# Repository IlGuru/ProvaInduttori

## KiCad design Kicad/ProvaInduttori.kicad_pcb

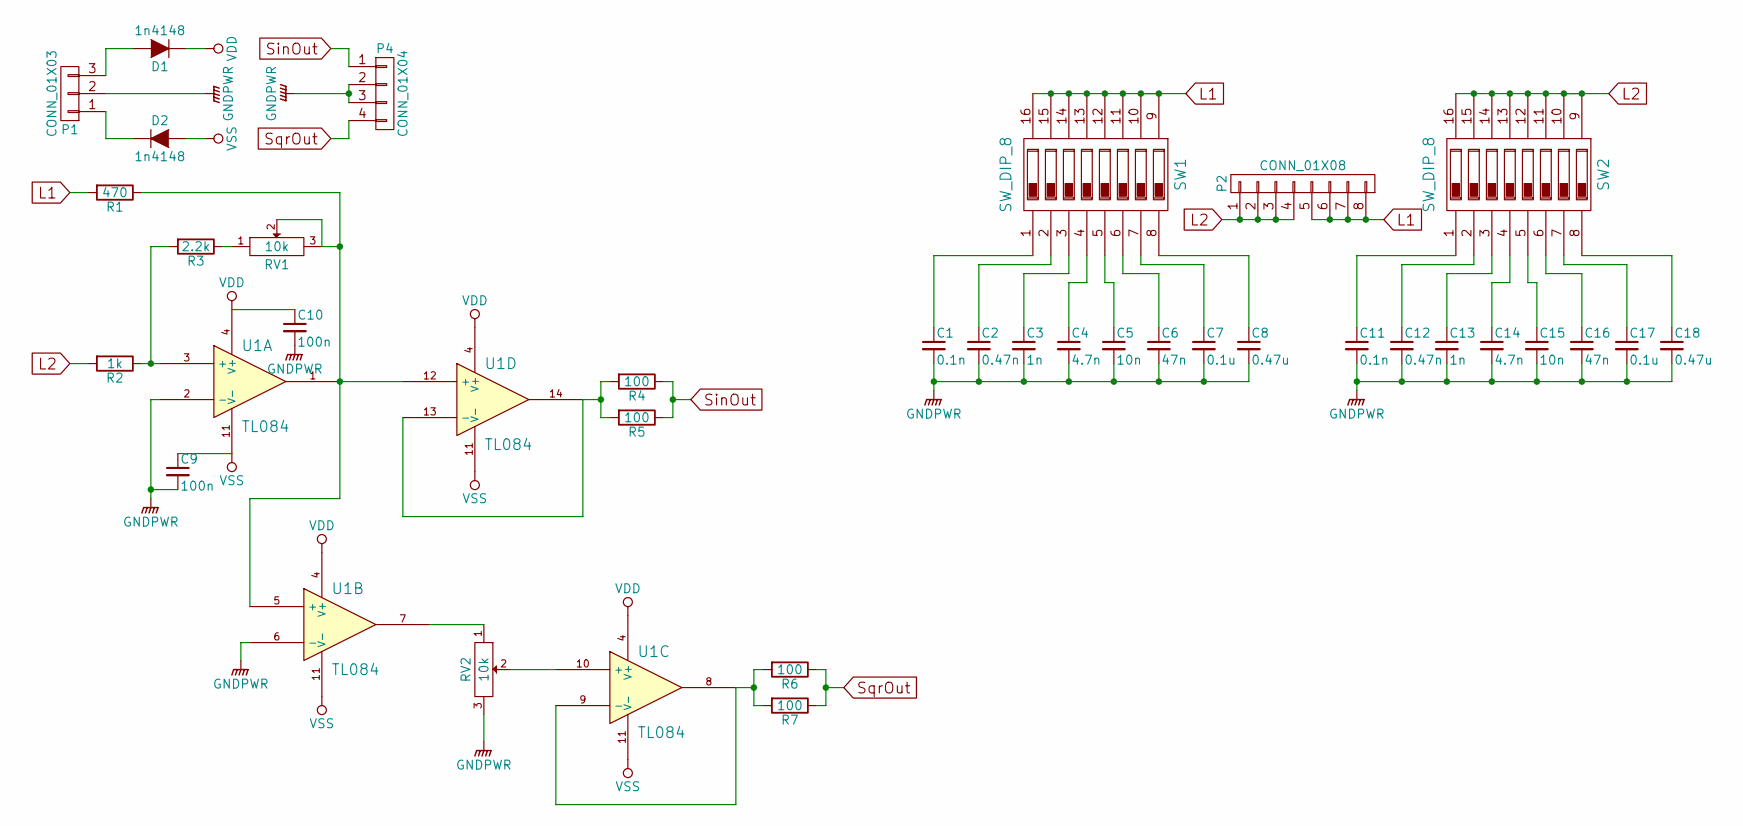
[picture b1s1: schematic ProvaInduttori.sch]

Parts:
C1, C11: 0.1n; C_Rect_L7_W2.5_P5
C2, C12: 0.47n; C_Rect_L7_W2.5_P5
C3, C13: 1n; C_Rect_L7_W2.5_P5
C4, C14: 4.7n; C_Rect_L7_W2.5_P5
C5, C15: 10n; C_Rect_L7_W2.5_P5
C6, C16: 47n; C_Rect_L7_W2.5_P5
C7, C17: 0.1u; C_Rect_L7_W2.5_P5
C8, C18: 0.47u; C_Rect_L7_W2.5_P5
C9, C10: 100n; C_Rect_L7_W2.5_P5
D1, D2: 1n4148; Diode_DO-35_SOD27_Horizontal_RM10
P1: CONN_01X03; Pin_Header_Straight_1x03
P2: CONN_01X08; Pin_Header_Straight_1x08
P4: CONN_01X04; Pin_Header_Straight_1x04
R1: 470; Resistor_Horizontal_RM10mm
R2: 1k; Resistor_Horizontal_RM10mm
R3: 2.2k; Resistor_Horizontal_RM10mm
R4, R5, R6, R7: 100; Resistor_Horizontal_RM10mm
RV1, RV2: 10k; Potentiometer_Bourns_3386G-1-103LF
SW1, SW2: SW_DIP_8; DIP-16_W7.62mm_LongPads
U1: TL084; DIP-14_W7.62mm_LongPads

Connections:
GNDPWR: C1.2, C2.2, C3.2, C4.2, C5.2, C6.2, C7.2, C8.2, C9.2, C10.2, C11.2, C12.2, C13.2, C14.2, C15.2, C16.2, C17.2, C18.2, P1.2, P4.2, P4.3, RV2.3, U1.2 (-), U1.6 (-)
L1: P2.5, P2.6, P2.7, P2.8, R1.2, SW1.9, SW1.10, SW1.11, SW1.12, SW1.13, SW1.14, SW1.15, SW1.16
L2: P2.1, P2.2, P2.3, P2.4, R2.2, SW2.9, SW2.10, SW2.11, SW2.12, SW2.13, SW2.14, SW2.15, SW2.16
unnamed: C1.1, SW1.1
unnamed: C2.1, SW1.2
unnamed: C3.1, SW1.3
unnamed: C4.1, SW1.4
unnamed: C5.1, SW1.5
unnamed: C6.1, SW1.6
unnamed: C7.1, SW1.7
unnamed: C8.1, SW1.8
unnamed: C11.1, SW2.1
unnamed: C12.1, SW2.2
unnamed: C13.1, SW2.3
unnamed: C14.1, SW2.4
unnamed: C15.1, SW2.5
unnamed: C16.1, SW2.6
unnamed: C17.1, SW2.7
unnamed: C18.1, SW2.8
unnamed: D1.2 (A), P1.3
unnamed: D2.1 (K), P1.1
unnamed: R1.1, RV1.2, RV1.3, U1.1, U1.5 (+), U1.12 (+)
unnamed: R2.1, R3.2, U1.3 (+)
unnamed: R3.1, RV1.1
unnamed: R4.2, R5.2, U1.13 (-), U1.14
unnamed: R6.2, R7.2, U1.8, U1.9 (-)
unnamed: RV2.1, U1.7
unnamed: RV2.2, U1.10 (+)
SinOut: P4.1, R4.1, R5.1
SqrOut: P4.4, R6.1, R7.1
VDD: C10.1, D1.1 (K), U1.4 (V+)
VSS: C9.1, D2.2 (A), U1.11 (V-)

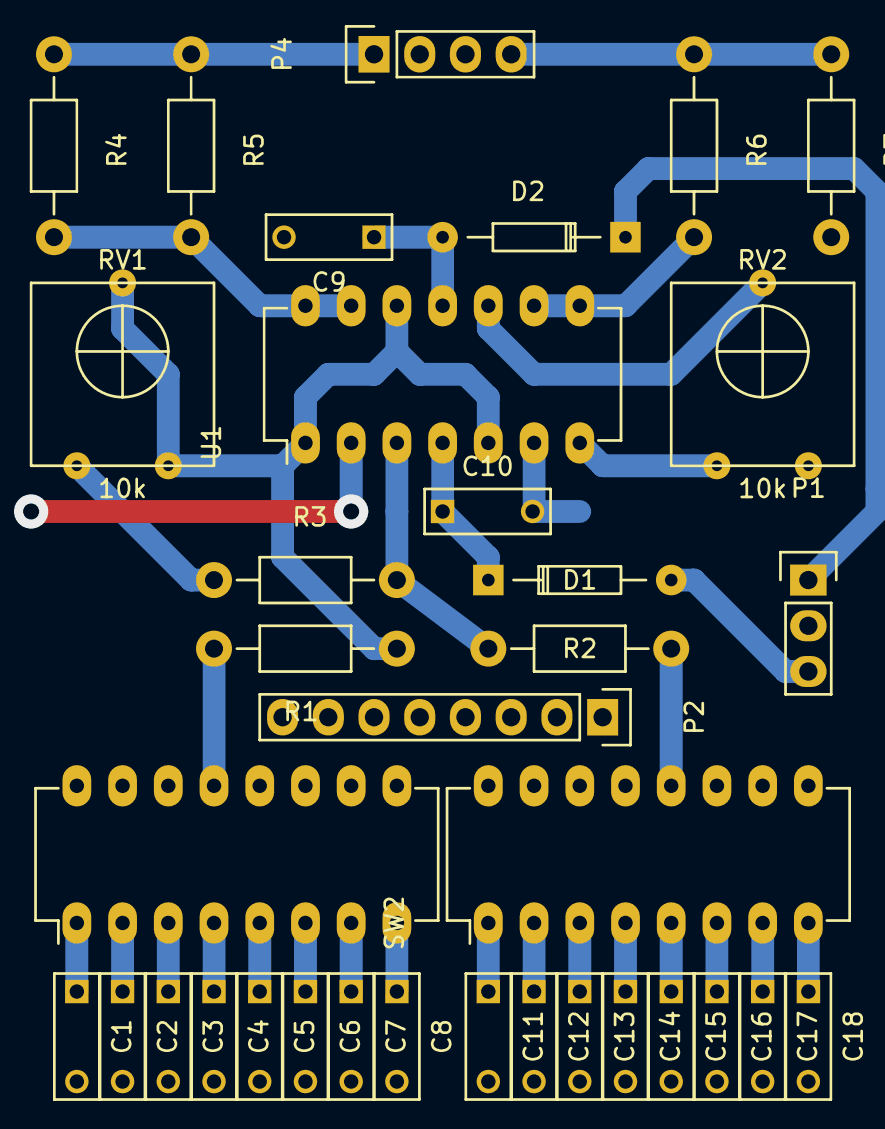
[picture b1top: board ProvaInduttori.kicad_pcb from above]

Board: 2 copper layers, 35 parts (0 on the bottom side), 32 nets.
